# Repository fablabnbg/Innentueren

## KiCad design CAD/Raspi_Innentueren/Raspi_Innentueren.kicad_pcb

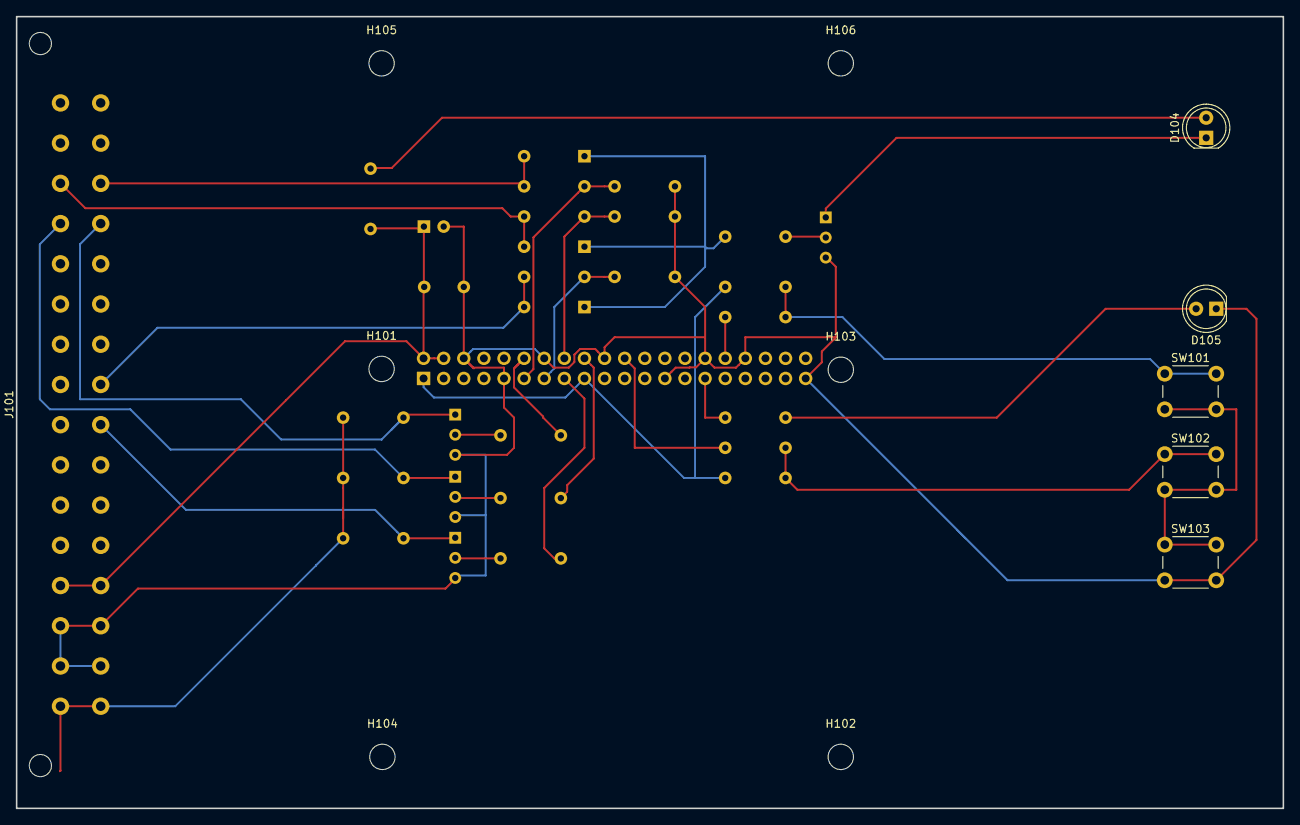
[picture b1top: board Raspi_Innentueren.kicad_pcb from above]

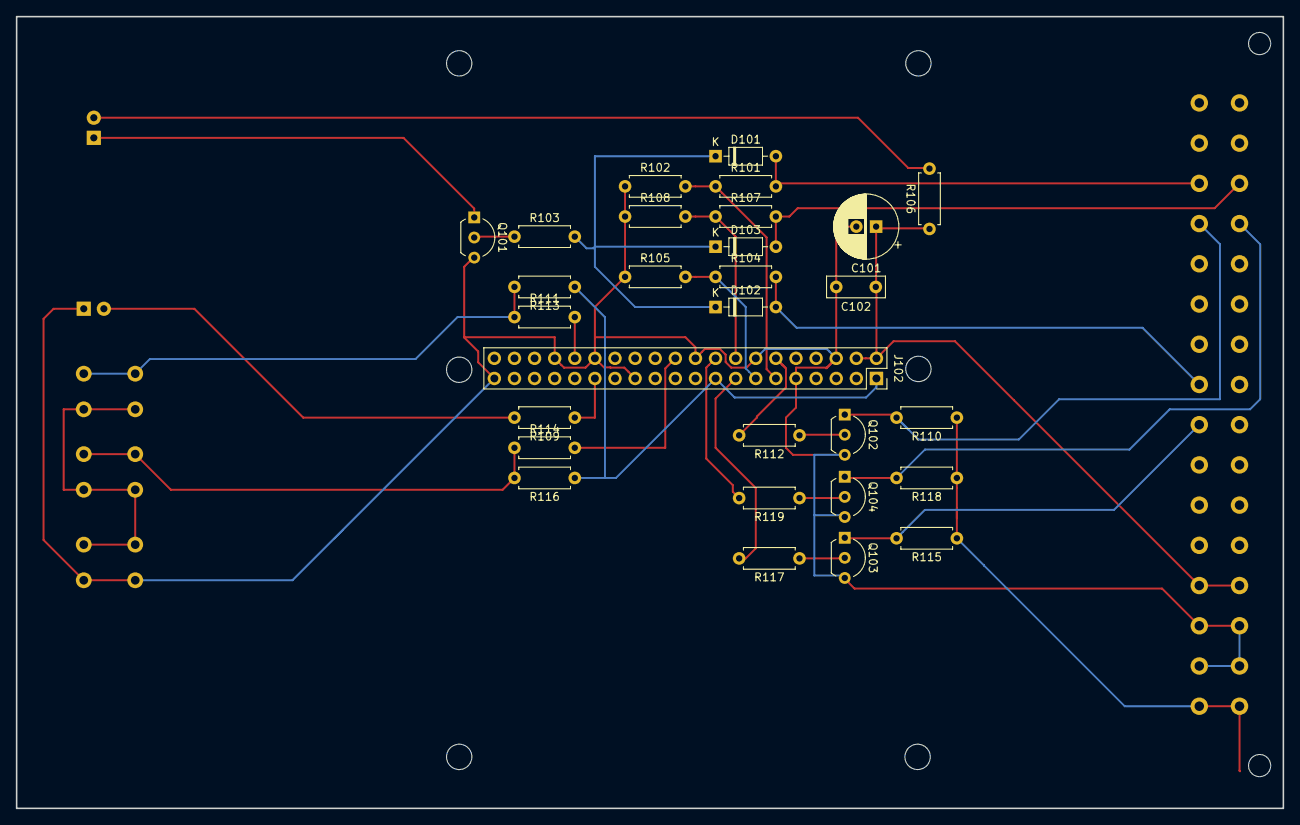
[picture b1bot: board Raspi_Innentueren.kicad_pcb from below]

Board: 2 copper layers, 160.0 x 100.0 mm, 41 parts (29 on the bottom side), 30 nets.

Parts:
C101: 100u/16V; CP_Radial_D8.0mm_P2.50mm
C102: 100n/16V; C_Rect_L7.2mm_W2.5mm_P5.00mm_FKS2_FKP2_MKS2_MKP2
D101, D102, D103: D_Small; D_DO-35_SOD27_P7.62mm_Horizontal
D104: rt; LED_D5.0mm_Clear
D105: gn; LED_D5.0mm_Clear
H101, H102, H103, H104, H105, H106: MountingHole; MountingHole_3.2mm_M3
J101: Conn_02x16_Letter_AC; DIN41612_D_32pol_90deg
J102: Conn_02x20_Odd_Even; PinSocket_2x20_P2.54mm_Vertical
Q101, Q102, Q103, Q104: Q_NPN_CBE; TO-92L_Inline_Wide
R101, R104, R107: 20k; R_Axial_DIN0207_L6.3mm_D2.5mm_P7.62mm_Horizontal
R102, R105, R108: 39k; R_Axial_DIN0207_L6.3mm_D2.5mm_P7.62mm_Horizontal
R103, R111, R112, R114, R117, R119: 1k; R_Axial_DIN0207_L6.3mm_D2.5mm_P7.62mm_Horizontal
R106: 330R; R_Axial_DIN0207_L6.3mm_D2.5mm_P7.62mm_Horizontal
R109: 120R; R_Axial_DIN0207_L6.3mm_D2.5mm_P7.62mm_Horizontal
R110, R113, R115, R116, R118: 10k; R_Axial_DIN0207_L6.3mm_D2.5mm_P7.62mm_Horizontal
SW101, SW102, SW103: SW_Push; SW_PUSH_6mm

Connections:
+3V3: J102.1, J102.17, R113.1, R116.1
+5V: C101.1, C102.1, J101.26a, J101.26c, J102.2, J102.4, R106.1
+12V: J101.32a, J101.32c, R110.1, R115.1, R118.1
/Run: J102.29, R109.1
/T1_Err_3V3: J102.11, R101.1, R102.2
/T1_Error: D101.2, J101.6a, R101.2
/T1_PWR_EN_3V3: J102.12, R112.2
/T2_Err_3V3: J102.13, R104.1, R105.2
/T2_Error: D102.2, J101.16a, R104.2
/T2_PWR_EN_3V3: J102.15, R117.2
/T3_Err_3V3: J102.16, R107.1, R108.2
/T3_Error: D103.2, J101.6c, R107.2
/T3_PWR_EN_3V3: J102.18, R119.2
/~Check~: J102.32, R111.2
/~Reboot: J102.22, R114.2
/~T1_PWR_EN~: J101.8a, Q102.1, R110.2
/~T2_PWR_EN~: J101.18a, Q103.1, R115.2
/~T3_PWR_EN~: J101.8c, Q104.1, R118.2
GND: C101.2, C102.2, D105.1, J101.28a, J101.28c, J101.30a, J101.30c, J102.6, J102.9, J102.14, J102.20, J102.25, J102.30, J102.34, J102.39, Q101.3, Q102.3, Q103.3, Q104.3, R102.1, R105.1, R108.1, SW103.2
unnamed: D101.1, D102.1, D103.1, R103.2
unnamed: D104.1, Q101.1
unnamed: D104.2, R106.2
unnamed: D105.2, R109.2
unnamed: Q101.2, R103.1
unnamed: Q102.2, R112.1
unnamed: Q103.2, R117.1
unnamed: Q104.2, R119.1
unnamed: R111.1, R113.2, SW101.1
unnamed: R114.1, R116.2, SW102.1
unnamed: SW101.2, SW102.2, SW103.1

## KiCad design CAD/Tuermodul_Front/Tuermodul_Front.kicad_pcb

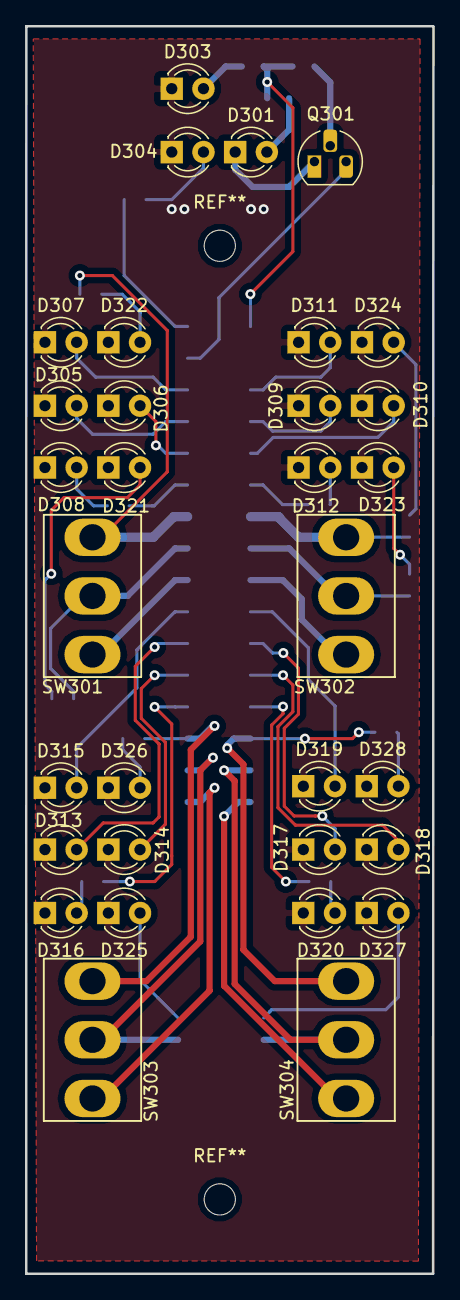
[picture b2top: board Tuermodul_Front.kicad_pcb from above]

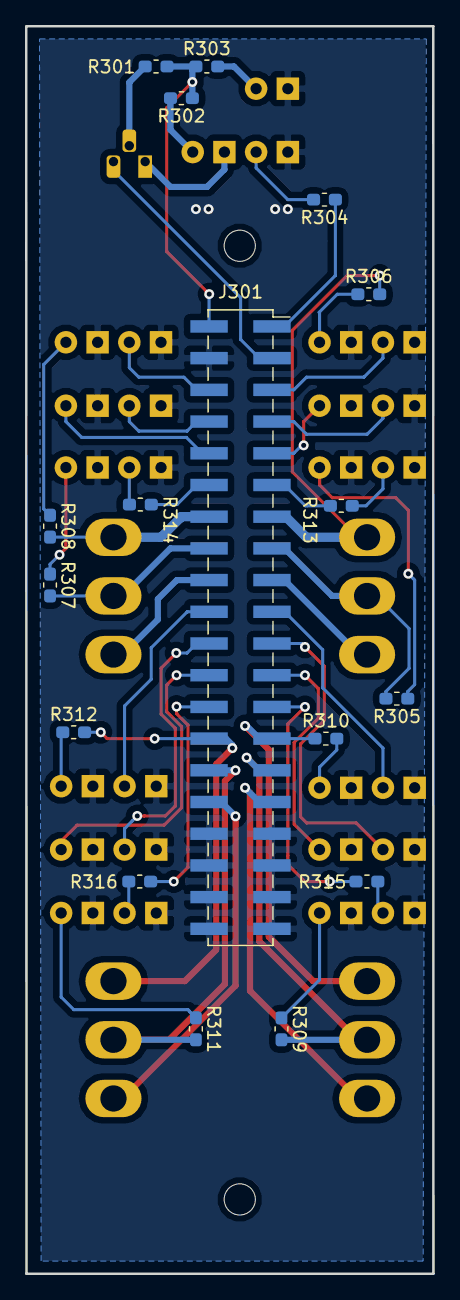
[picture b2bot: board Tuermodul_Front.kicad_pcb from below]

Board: 2 copper layers, 32.6 x 100.0 mm, 49 parts (17 on the bottom side), 49 nets.

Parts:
D301, D303, D304, D305, D307, D308, D309, D311, D312, D313, D315, D316, D317, D319, D320, D321, D322, D323, D324, D325, D326, D327, D328: rt; LED_D3.0mm
D306, D310, D314, D318: gn; LED_D3.0mm
J301: Conn_02x20_Counter_Clockwise; PinSocket_2x20_P2.54mm_Vertical_SMD
Q301: Q_NPN_CBE; TO-92_HandSolder
R301, R304: 1k; R_0603_1608Metric_Pad1.05x0.95mm_HandSolder
R302, R303: 330R; R_0603_1608Metric_Pad1.05x0.95mm_HandSolder
R305, R306, R307, R308, R309, R310, R311, R312: 4k7; R_0603_1608Metric_Pad1.05x0.95mm_HandSolder
R313, R314, R315, R316: 470R; R_0603_1608Metric_Pad1.05x0.95mm_HandSolder
SW301, SW302, SW303, SW304: SW_SPDT_MSM; SPDT

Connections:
+5P: J301.2, R301.1, R302.1, R303.1
+12P: J301.1, R304.1
/Front/DA_Rx: D306.2, J301.9
/Front/DA_Tx: D305.2, J301.7
/Front/DB_Rx: D310.2, J301.10
/Front/DB_Tx: D309.2, J301.8
/Front/DC_Rx: D314.2, J301.23
/Front/DC_Tx: D313.2, J301.21
/Front/DD_Rx: D318.2, J301.24
/Front/DD_Tx: D317.2, J301.22
/Front/DoorA_12V: J301.13, R306.2, SW301.1
/Front/DoorA_Auto: J301.17, SW301.3
/Front/DoorA_Lock: J301.15, R305.2, SW301.2
/Front/DoorA_MK: J301.11, R313.2
/Front/DoorA_VCC: D307.2, J301.5
/Front/DoorB_12V: J301.14, R308.2, SW302.1
/Front/DoorB_Auto: J301.18, SW302.3
/Front/DoorB_Lock: J301.16, R307.2, SW302.2
/Front/DoorB_MK: J301.12, R314.2
/Front/DoorB_VCC: D311.2, J301.6
/Front/DoorC_12V: J301.27, R310.2, SW303.1
/Front/DoorC_Auto: J301.31, SW303.3
/Front/DoorC_Lock: J301.29, R309.2, SW303.2
/Front/DoorC_MK: J301.25, R315.2
/Front/DoorC_VCC: D315.2, J301.19
/Front/DoorD_12V: J301.28, R312.2, SW304.1
/Front/DoorD_Auto: J301.32, SW304.3
/Front/DoorD_Lock: J301.30, R311.2, SW304.2
/Front/DoorD_MK: J301.26, R316.2
/Front/DoorD_VCC: D319.2, J301.20
/Front/Fuse_Error: J301.3, Q301.3
GNDA: D303.1, D304.1, D305.1, D306.1, D307.1, D308.1, D309.1, D310.1, D311.1, D312.1, D313.1, D314.1, D315.1, D316.1, D317.1, D318.1, D319.1, D320.1, D321.1, D322.1, D323.1, D324.1, D325.1, D326.1, D327.1, D328.1, J301.4, J301.33, J301.34, J301.35, J301.36, J301.37, J301.38, J301.39, J301.40
unnamed: D301.1, Q301.1
unnamed: D301.2, R302.2
unnamed: D303.2, R303.2
unnamed: D304.2, R304.2
unnamed: D308.2, R313.1
unnamed: D312.2, R314.1
unnamed: D316.2, R315.1
unnamed: D320.2, R316.1
unnamed: D321.2, R305.1
unnamed: D322.2, R306.1
unnamed: D323.2, R307.1
unnamed: D324.2, R308.1
unnamed: D325.2, R309.1
unnamed: D326.2, R310.1
unnamed: D327.2, R311.1
unnamed: D328.2, R312.1
unnamed: Q301.2, R301.2

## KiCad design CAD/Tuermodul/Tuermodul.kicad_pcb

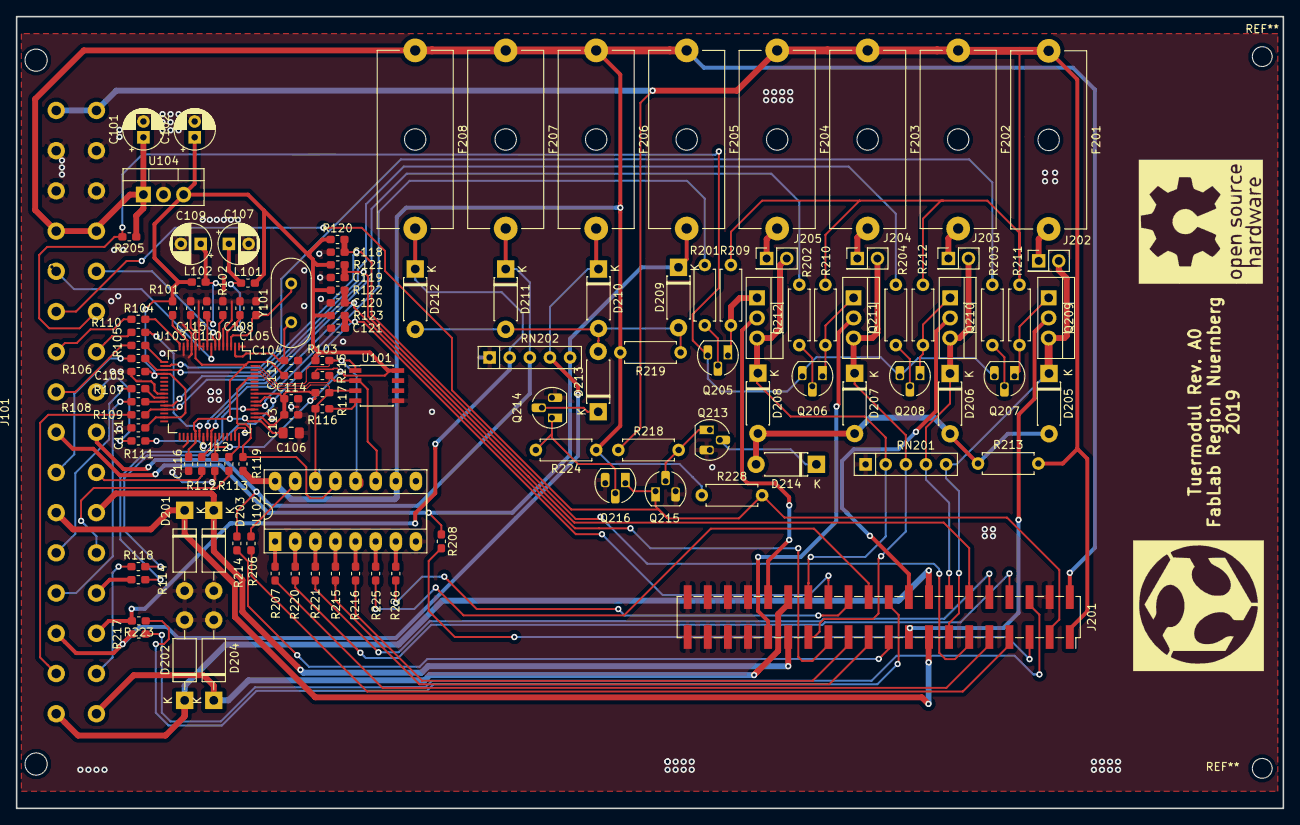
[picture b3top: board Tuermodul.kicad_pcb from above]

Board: 2 copper layers, 160.0 x 100.0 mm, 121 parts (0 on the bottom side), 102 nets.

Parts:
C101, C102: 1u; CP_Radial_D5.0mm_P2.00mm
C103, C108, C110, C111, C112, C113, C114, C115, C116, C117, C118, C119, C120, C121: 100n; C_0603_1608Metric_Pad1.05x0.95mm_HandSolder
C104, C105: 27p; C_0603_1608Metric_Pad1.05x0.95mm_HandSolder
C106: 3u3; C_0805_2012Metric_Pad1.15x1.40mm_HandSolder
C107, C109: 4u7; CP_Radial_D5.0mm_P2.50mm
D201, D202, D203, D204: 1N4007; D_DO-41_SOD81_P10.16mm_Horizontal
D205, D206, D207, D208, D209, D210, D211, D212, D213, D214: 1N4148; D_DO-41_SOD81_P7.62mm_Horizontal
F201, F202, F203, F204: 1A; Fuseholder_Cylinder-5x20mm_Schurter_0031_8201_Horizontal_Op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
F205, F206, F207, F208: 0.5A; Fuseholder_Cylinder-5x20mm_Schurter_0031_8201_Horizontal_Op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
G101: LOGO; fln_logo
G102: LOGO; OSH_logo
J101: Conn_02x16_Counter_Clockwise; DIN41612_D_32pol_90deg
J201: Conn_02x20_Odd_Even; PinSocket_2x20_P2.54mm_Vertical_SMD
J202, J203, J204, J205: Conn_02x01; PinHeader_2x01_P2.54mm_Vertical
L101, L102: 600R/0.5A; L_0603_1608Metric_Pad1.05x0.95mm_HandSolder
Q205, Q206, Q207, Q208, Q213, Q214, Q215, Q216: Q_NPN_CBE; TO-92_HandSolder
Q209, Q210, Q211, Q212: Q_PMOS_GDS; TO-220-3_Vertical
R101, R120, R121, R122, R123, R206, R207, R208, R214, R215, R216, R217, R220, R221, R223, R225, R226: 1k; R_0603_1608Metric_Pad1.05x0.95mm_HandSolder
R102: 12k; R_0603_1608Metric_Pad1.05x0.95mm_HandSolder
R103, R115, R117, R119, R205: 10k; R_0603_1608Metric_Pad1.05x0.95mm_HandSolder
R104, R105, R107, R108, R110, R111, R113, R114: 33R; R_0603_1608Metric_Pad1.05x0.95mm_HandSolder
R106, R109, R112, R118: 100R; R_0603_1608Metric_Pad1.05x0.95mm_HandSolder
R116: 2k; R_0603_1608Metric_Pad1.05x0.95mm_HandSolder
R201, R202, R203, R204: 1k; R_Axial_DIN0207_L6.3mm_D2.5mm_P7.62mm_Horizontal
R209, R210, R211, R212: 100k; R_Axial_DIN0207_L6.3mm_D2.5mm_P7.62mm_Horizontal
R213, R219: 1M; R_Axial_DIN0207_L6.3mm_D2.5mm_P7.62mm_Horizontal
R218, R224, R228: 10k; R_Axial_DIN0207_L6.3mm_D2.5mm_P7.62mm_Horizontal
RN201, RN202: 4x10k; R_Array_SIP5
U101: 93LC46B; SOIC-8_3.9x4.9mm_P1.27mm
U102: 74HC595; DIP-16_W7.62mm_Socket_LongPads
U103: FT4232H; LQFP-64_10x10mm_P0.5mm
U104: MCP1825S; TO-220-3_Vertical
Y101: 12MHz; Crystal_HC18-U_Vertical

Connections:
+1V8: C106.1, C115.1, C116.1, C117.1, U103.12, U103.37, U103.49, U103.64
+3V3: C102.1, C103.1, C111.1, C112.1, C113.1, C114.1, L101.2, L102.2, R101.1, R103.1, R115.1, R117.1, R120.1, R121.1, R122.1, R123.1, U101.8, U103.20, U103.31, U103.42, U103.50, U103.56, U104.3
+5V: C101.1, F205.1, F206.1, F207.1, F208.1, J101.4, J101.29, J201.2, R119.1, R205.1, R219.2, R224.1, R228.1, U102.10, U102.16, U104.1
+12V: F201.1, F202.1, F203.1, F204.1, J101.1, J101.32, J201.1, R209.2, R210.2, R211.2, R212.2, R213.2, R218.1
/D+: J101.5, U103.8
/D-: J101.28, U103.7
/DA_Rx: R207.1, U102.1
/DA_Tx: R206.1, U102.15
/DB_Rx: R221.2, U102.3
/DB_Tx: R220.2, U102.2
/DC_Rx: R216.1, U102.5
/DC_Tx: R215.1, U102.4
/DD_Rx: R226.2, U102.7
/DD_Tx: R225.2, U102.6
/DoorA_Lock: D201.1, J101.11, J201.15
/DoorA_MK: C118.1, J201.11, R106.1, R120.2, U103.19
/DoorA_RTS: R203.2, U103.18
/DoorA_RX_DTE: R105.1, U103.17
/DoorA_TX_DTE: R104.1, U103.16
/DoorA_VCC: D209.1, F205.2, J101.9, R208.1, RN202.5
/DoorB_Lock: D202.1, J101.16, J201.16
/DoorB_MK: C119.1, J201.12, R109.1, R121.2, U103.29
/DoorB_RTS: R204.2, U103.28
/DoorB_RX_DTE: R108.1, U103.27
/DoorB_TX_DTE: R107.1, U103.26
/DoorB_VCC: D210.1, F206.2, J101.14, R217.2, RN202.4
/DoorC_Lock: D203.1, J101.22, J201.29
/DoorC_MK: C120.1, J201.25, R112.2, R122.2, U103.41
/DoorC_RTS: R202.2, U103.40
/DoorC_RX_DTE: R111.2, U103.39
/DoorC_TX_DTE: R110.2, U103.38
/DoorC_VCC: D211.1, F207.2, J101.24, R214.1, RN202.3
/DoorD_Lock: D204.1, J101.17, J201.30
/DoorD_MK: C121.1, J201.26, R118.2, R123.2, U103.54
/DoorD_RTS: R201.2, U103.53
/DoorD_RX_DTE: R114.2, U103.52
/DoorD_TX_DTE: R113.2, U103.48
/DoorD_VCC: D212.1, F208.2, J101.19, R223.2, RN202.2
/EECLK: R115.2, U101.2, U102.11, U103.62
/EECS: R103.2, U101.1, U102.12, U103.63
/EEDATA: R116.2, R117.2, U101.3, U102.14, U103.61
/Error: J101.6, J201.3, Q215.1, Q216.1, R228.2
/Peripherie/DoorA_12V: D205.1, J201.13, J202.2, Q209.3, RN201.5
/Peripherie/DoorA_Auto: J201.17, Q209.2
/Peripherie/DoorB_12V: D206.1, J201.14, J203.2, Q210.3, RN201.4
/Peripherie/DoorB_Auto: J201.18, Q210.2
/Peripherie/DoorC_12V: D207.1, J201.27, J204.2, Q211.3, RN201.3
/Peripherie/DoorC_Auto: J201.31, Q211.2
/Peripherie/DoorD_12V: D208.1, J201.28, J205.2, Q212.3, RN201.2
/Peripherie/DoorD_Auto: J201.32, Q212.2
/~PWREN~: R119.2, U102.13, U103.60
/~PWR_EN~: J101.27, Q205.3, Q206.3, Q207.3, Q208.3, R205.2
GND: C101.2, C102.2, C103.2, C104.2, C105.2, C106.2, C107.2, C108.2, C109.2, C110.2, C111.2, C112.2, C113.2, C114.2, C115.2, C116.2, C117.2, C118.2, C119.2, C120.2, C121.2, D201.2, D202.2, D203.2, D204.2, J101.2, J101.3, J101.30, J101.31, J201.4, J201.33, J201.34, J201.35, J201.36, J201.37, J201.38, J201.39, J201.40, Q213.3, Q214.3, Q215.3, Q216.3, R102.1, RN201.1, RN202.1, U101.5, U102.8, U103.1, U103.5, U103.10, U103.11, U103.13, U103.15, U103.25, U103.35, U103.47, U103.51, U104.2
unnamed: C104.1, U103.2, Y101.1
unnamed: C105.1, U103.3, Y101.2
unnamed: C107.1, C108.1, L101.1, U103.4
unnamed: C109.1, C110.1, L102.1, U103.9
unnamed: D205.2, D206.2, D207.2, D208.2, D214.2, R213.1
unnamed: D209.2, D210.2, D211.2, D212.2, D213.2, R219.1
unnamed: D213.1, Q214.2
unnamed: D214.1, Q213.2
unnamed: F201.2, J202.1
unnamed: F202.2, J203.1
unnamed: F203.2, J204.1
unnamed: F204.2, J205.1
unnamed: J101.7, R104.2
unnamed: J101.8, R105.2
unnamed: J101.10, R106.2
unnamed: J101.12, R107.2
unnamed: J101.13, R108.2
unnamed: J101.15, R109.2
unnamed: J101.18, R118.1
unnamed: J101.20, R114.1
unnamed: J101.21, R113.1
unnamed: J101.23, R112.1
unnamed: J101.25, R111.1
unnamed: J101.26, R110.1
unnamed: J201.5, R208.2
unnamed: J201.6, R217.1
unnamed: J201.7, R206.2
unnamed: J201.8, R220.1
unnamed: J201.9, R207.2
unnamed: J201.10, R221.1
unnamed: J201.19, R214.2
unnamed: J201.20, R223.1
unnamed: J201.21, R215.2
unnamed: J201.22, R225.1
unnamed: J201.23, R216.2
unnamed: J201.24, R226.1
unnamed: Q205.1, Q212.1, R209.1
unnamed: Q205.2, R201.1
unnamed: Q206.1, Q211.1, R210.1
unnamed: Q206.2, R202.1
unnamed: Q207.1, Q209.1, R211.1
unnamed: Q207.2, R203.1
unnamed: Q208.1, Q210.1, R212.1
unnamed: Q208.2, R204.1
unnamed: Q213.1, Q215.2, R218.2
unnamed: Q214.1, Q216.2, R224.2
unnamed: R101.2, U103.14
unnamed: R102.2, U103.6
unnamed: R116.1, U101.4

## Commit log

2019-01-22 -mod: first commit of schematic and layout
2019-01-29 -add: Fuse Error, missing LEDs -mod: some Resistor footprints changed -mod: first placement in layout
2019-01-31 -add: TechSpec ins Git umgezogen
2019-01-31 -add: Front.sch for front panel -mod: moved leds and switches to front panel -mod: added MK contacts (not finished jet) -mod: added switches
2019-02-07 Arduino-Project for the MFRC522 RFID Cardreader
2019-02-08 -add: Kartenleser Doku -mod: Cardreader_522 made changes sugested by Patrick H. -mod: Cardreader_522 added some comments -mod: Cardreader_522 corrected Commnts regarding LED colors
2019-02-08 Remove canaries
    Remove the markers and the explicit command counting from the ringbuffer and replace them with calculations on the read and write pointers. This also allows an uninitialised buffer.
2019-02-08 -mod Cardreader_522: Fixed wrong shift
2019-02-09 -mod Fixed Race condition (atmega328 has no 8bit increment / decrement commands)
2019-02-10 -add: switch library for spdt switches -mod: improvements in schematic, bugfixes -mod: placement and routing of the ftdi chip + chicken food
2019-02-10 -add Cardreader_532 Arduino Programm
2019-02-10 -add Missing PN532 libraries
2019-02-13 -mod: layout tuermodul
2019-02-15 -mod Cleanup Cardreader_522 Software -mod Add Hardware Reset to Reader in Cardreader_522 Software
2019-02-16 -mod: adapted TechSpec due to power enable discussion -mod: changed pin header for front-to-main panel connection -mod: general layout work
2019-03-07 mod:layout work
2019-03-10 -mod: Umbelegung Stecker zwischen Haupt und Frontplatine -add: 100n caps für MK Entprellung -mod: Routing Stecker -mod: Platzierung Front nach Vorgabe
2019-03-13 -mod: layout update from 10.03.19
2019-03-26 -mod: Änderungen aus Review in Schaltplan und Layout
2019-03-29 -mod: DIN Stecker auf Typ D geändert. Layout angepasst und optimiert.
2019-03-31 -add: BOM -mod: letzte Schritte für LP Hersteller, Gerber Dateien für A0 generiert.
2019-04-15 -mod: Front und Hauptplatine separiert -mod: BOM von Nicolas überarbeitet
2019-04-24 -BOM: Teile rausgesucht.
2019-10-14 -add: KiCAD project Raspi Innentueren
2019-10-14 -mod: bugfixed mounting holes
2019-10-16 -bug: fixed bugs in raspi schematic -mod: added confirm button and additional check button -mod: PWR_EN signals shifted from 3V3 to 12V level via transistor
2019-11-04 -mod: layout Raspi Platine fertiggestellt
2019-11-04 -mod: raspi stecker nach oben und links verschoben, mountingholes hinzugefügt
2019-11-11 -mod: update shield layout
2020-03-15 -add: Mechanik für Kartenleser hinzugefuegt
2021-06-15 -add: Innentüren Python scripts
2021-07-04 PDF-Files for schematics and pcbs Signed-off-by: Juergen G. Schimmer <schimmi2@gmail.com>
2021-09-15 added initial draft of podio-nfc-pull.py
2021-09-15 date and "author" added.
2021-12-05 podio_app_id = '13414993' lost all innentüren. Only a Besitzer-FobNr-HexId relation remains.
    Disabled the json output generator, added a generic app dumper for now.
2021-12-06 exercising filter, to access a specific list of items from an app... We can use that to query only those items from te Mitglieder app that are referenced by an NFC item.
2023-11-30 -mod: moved the Cardreader PDF file
